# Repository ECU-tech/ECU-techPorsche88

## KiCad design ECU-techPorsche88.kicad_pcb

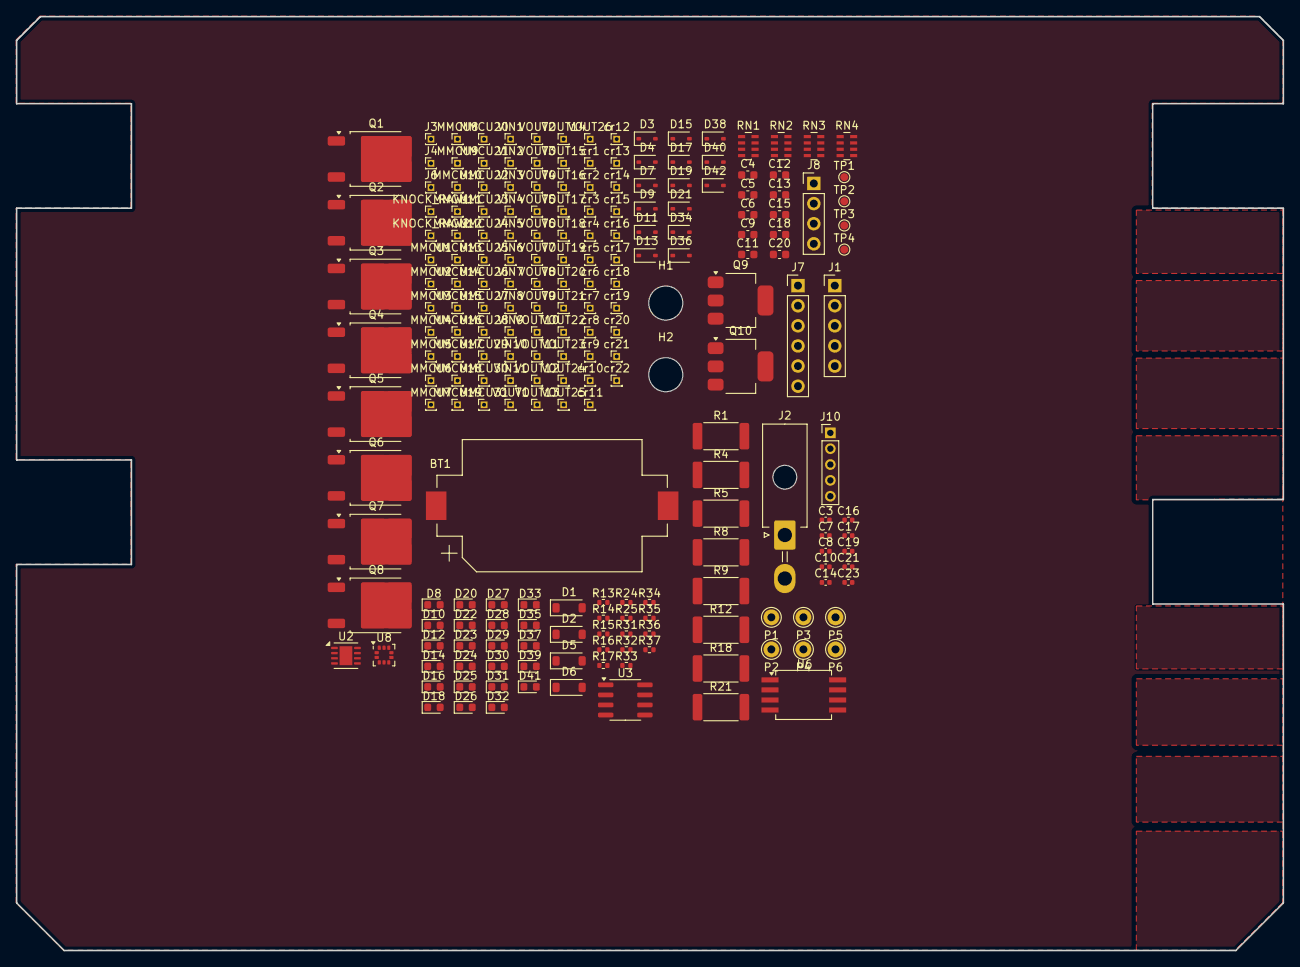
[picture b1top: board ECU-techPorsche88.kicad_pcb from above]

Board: 4 copper layers, 160.0 x 118.0 mm, 215 parts (0 on the bottom side), 69 nets, no tracks yet.

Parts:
BT1: BATTERY_CR2032; BatteryHolder_Keystone_1060_1x2032
C3, C7, C16, C17, C19, C21, C23: 100nF; C_0402_1005Metric
C4, C5, C6, C9, C11, C12, C13, C15, C18, C20: 10u; C_0603_1608Metric
C8: 5.6nF; C_0402_1005Metric
C10: 10nF; C_0402_1005Metric
C14: 220nF; C_0402_1005Metric
D1, D2, D5, D6: B5819W; D_SOD-123
D3, D4, D7, D9, D11, D13, D15, D17, D19, D21, D34, D36, D38, D40, D42: 1N4148WS; D_SOD-323
D8, D10, D12, D14, D16, D18, D20, D22, D37, D39: LED-RED-0603; LED_0603_1608Metric
D23, D24, D25, D26, D27, D28, D29, D30: LED-BLUE-0603; LED_0603_1608Metric
D31, D32, D33, D35: LED-GREEN-0603; LED_0603_1608Metric
D41: LED-WHITE-0603; LED_0603_1608Metric
H1, H2: MountingHole; MountingHole_4.3mm_M4_DIN965
J1: Conn_01x05; PinHeader_1x05_P2.54mm_Vertical
J2: MiniFit; Molex_Mini-Fit_Jr_5569-02A2_2x01_P4.20mm_Horizontal
J3: VRIN1; PinHeader_1x01_P1.00mm_Vertical
J4: VRIN2; PinHeader_1x01_P1.00mm_Vertical
J6: VROUT1; PinHeader_1x01_P1.00mm_Vertical
J7: ETB; PinHeader_1x06_P2.54mm_Vertical
J8: PPS; PinHeader_1x04_P2.54mm_Vertical
J10: Conn_01x05; PinHeader_1x05_P2.00mm_Vertical
KNOCK_RAW1: IN_KNOCK1_RAW; PinHeader_1x01_P1.00mm_Vertical
KNOCK_RAW2: IN_KNOCK2_RAW; PinHeader_1x01_P1.00mm_Vertical
MMCU1, MMCU2, MMCU3, MMCU4, MMCU5, MMCU6, MMCU7, MMCU8, MMCU9, MMCU10, MMCU11, MMCU12, MMCU13, MMCU14, MMCU15, MMCU16, MMCU17, MMCU18, MMCU19, MMCU20, MMCU21, MMCU22, MMCU23, MMCU24, MMCU25, MMCU26, MMCU27, MMCU28, MMCU29, MMCU30, MMCU31: MMCU; PinHeader_1x01_P1.00mm_Vertical
P1, P2, P3, P4, P5, P6: P; Pin_D1.0mm_L10.0mm
Q1, Q2, Q3, Q4, Q5, Q6, Q7, Q8: NGD8201AN; TO-252-2
Q9, Q10: AUIPS2041LTR; SOT-223
R1, R4, R5, R8, R9, R12, R18, R21: DNP; R_2512_6332Metric
R13, R14: DNP; R_0402_1005Metric
R15: 100k; R_0402_1005Metric
R16: 100; R_0402_1005Metric
R17, R24, R25: 10k; R_0402_1005Metric
R31: 1k6; R_0402_1005Metric
R32: 750R; R_0402_1005Metric
R33, R34, R35: 5k1; R_0402_1005Metric
R36: 20k; R_0402_1005Metric
R37: 4.7k; R_0402_1005Metric
RN1, RN2: 4.7k; R_Array_Concave_4x0603
RN3, RN4: 1k; R_Array_Concave_4x0603
TP1, TP2, TP3, TP4: TestPoint; TestPoint_Pad_D1.0mm
U2: TLS115_SON; HVSON-8-1EP_3x3mm_P0.65mm_EP1.6x2.4mm
U3: MCP6002-xSN; SOIC-8_3.9x4.9mm_P1.27mm
U6: MPXA6115A; SSO-8_6.8x5.9mm_P1.27mm_Clearance7mm
U8: LPS25HB; ST_HLGA-10_2.5x2.5mm_P0.6mm_LayoutBorder3x2y
VIN1: VIN9; PinHeader_1x01_P1.00mm_Vertical
VIN2, VIN3, VIN4, VIN5, VIN6, VIN7, VIN8: VIN8; PinHeader_1x01_P1.00mm_Vertical
VIN9: VIN10; PinHeader_1x01_P1.00mm_Vertical
VIN10: VIN16; PinHeader_1x01_P1.00mm_Vertical
VIN11: VIN17; PinHeader_1x01_P1.00mm_Vertical
VOUT1, VOUT2, VOUT3, VOUT4, VOUT5, VOUT6, VOUT7, VOUT8, VOUT9, VOUT10, VOUT11, VOUT12, VOUT14, VOUT15, VOUT16, VOUT17, VOUT19, VOUT20, VOUT21, VOUT22, VOUT23, VOUT24, VOUT25, VOUT26: VOUT4; PinHeader_1x01_P1.00mm_Vertical
VOUT13: VOUT5; PinHeader_1x01_P1.00mm_Vertical
VOUT18: VOUT6; PinHeader_1x01_P1.00mm_Vertical
cr1, cr2, cr3, cr4, cr5, cr6, cr7, cr8, cr9, cr10, cr11, cr12, cr13, cr14, cr15, cr16, cr17, cr18, cr19, cr20, cr21, cr22: cr; PinHeader_1x01_P1.00mm_Vertical

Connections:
+3V3: C23.1, D32.2 (A), J1.3, TP3.1, U8.1 (VDDio), U8.6 (~CS), U8.10 (VDD)
+5V: C3.1, D31.2 (A), J1.4, R37.1, TP2.1, U2.5 (ADJ), U3.8 (V+)
+5VA: C7.1, C17.1, U6.2 (Vcc)
+5VP: J7.1, J7.2, J8.1, U2.1 (OUT)
+12V: D33.2 (A), D34.1 (K), TP4.1
+12V_RAW: C6.1, C9.1, C11.1, C12.1, C13.1, C14.1, C15.1, C16.1, C18.1, C19.1, C20.1, D1.1 (K), D2.1 (K), D3.2 (A), D5.1 (K), D6.1 (K), D35.2 (A), D36.1 (K), J1.5, R36.1
/12V_prot: RN1.1 (R1.1), RN1.2 (R2.1), RN1.3 (R3.1), RN1.4 (R4.1), RN2.1 (R1.1), RN2.2 (R2.1), RN2.3 (R3.1), RN2.4 (R4.1), U2.7 (EN), U2.8 (IN), VOUT18.1
/COIL_1: Q1.2 (C), R1.1
/COIL_2: Q5.2 (C), R9.1
/COIL_3: Q4.2 (C), R8.2
/COIL_4: Q3.2 (C), R5.1
/COIL_5: Q2.2 (C), R4.2
/COIL_6: Q6.2 (C), R12.2
/COIL_7: Q7.2 (C), R18.1
/COIL_8: Q8.2 (C), R21.2
/ETB_EN: R15.2, R17.2
/ICV: Q9.1 (IN), R24.2
/IDLE: Q10.1 (IN), R25.2
/IN_CRANK: D41.1 (K), D42.2 (A), R13.2
/OUT_FUEL_PUMP_RELAY: D39.1 (K), D40.2 (A)
/OUT_ICV: D5.2 (A), Q9.2 (D), cr22.1
/OUT_IDLE: D6.2 (A), Q10.2 (D)
/OUT_IGN1: D30.2 (A), R1.2
/OUT_IGN2: D26.2 (A), R9.2
/OUT_IGN3: D29.2 (A), R8.1
/OUT_IGN4: D25.2 (A), R5.2
/OUT_IGN5: D28.2 (A), R4.1
/OUT_IGN6: D24.2 (A), R12.1
/OUT_IGN7: D27.2 (A), R18.2
/OUT_IGN8: D23.2 (A), R21.1
/OUT_INJ1: D7.2 (A), D8.1 (K)
/OUT_INJ2: D9.2 (A), D10.1 (K)
/OUT_INJ3: D11.2 (A), D12.1 (K)
/OUT_INJ4: D13.2 (A), D14.1 (K)
/OUT_INJ5: D15.2 (A), D16.1 (K)
/OUT_INJ6: D17.2 (A), D18.1 (K)
/OUT_INJ7: D19.2 (A), D20.1 (K)
/OUT_INJ8: D21.2 (A), D22.1 (K)
/OUT_MAIN_RELAY: D37.2 (A), D38.1 (K)
GND: BT1.2 (-), C3.2, C6.2, C7.2, C8.2, C9.2, C11.2, C12.2, C13.2, C15.2, C16.2, C17.2, C18.2, C19.2, C20.2, C21.2, C23.2, J1.1, J1.2, J7.5, J7.6, J8.4, J10.5, P1.1, Q1.3 (E), Q2.3 (E), Q3.3 (E), Q4.3 (E), Q5.3 (E), Q6.3 (E), Q7.3 (E), Q8.3 (E), Q9.3 (S), Q10.3 (S), R17.1, R24.1, R25.1, R31.2, R32.2, R33.2, R34.2, R35.2, RN3.1 (R1.1), RN3.2 (R2.1), RN3.3 (R3.1), RN3.4 (R4.1), RN4.1 (R1.1), RN4.2 (R2.1), RN4.3 (R3.1), RN4.4 (R4.1), TP1.1, U2.3 (GND), U2.9 (GND), U3.4 (V-), U6.3 (GND), U8.3 (GND), U8.5 (SA0/MISO), U8.8 (GND), U8.9 (GND)
unnamed: C10.1, R16.1
unnamed: D3.1 (K), D4.2 (A), R16.2
unnamed: C14.2, D4.1 (K)
unnamed: D7.1 (K), D8.2 (A), RN1.5 (R4.2)
unnamed: D9.1 (K), D10.2 (A), RN1.6 (R3.2)
unnamed: D11.1 (K), D12.2 (A), RN1.7 (R2.2)
unnamed: D13.1 (K), D14.2 (A), RN1.8 (R1.2)
unnamed: D15.1 (K), D16.2 (A), RN2.5 (R4.2)
unnamed: D17.1 (K), D18.2 (A), RN2.6 (R3.2)
unnamed: D19.1 (K), D20.2 (A), RN2.7 (R2.2)
unnamed: D21.1 (K), D22.2 (A), RN2.8 (R1.2)
unnamed: D23.1 (K), RN3.5 (R4.2)
unnamed: D24.1 (K), RN3.7 (R2.2)
unnamed: D25.1 (K), RN4.5 (R4.2)
unnamed: D26.1 (K), RN4.7 (R2.2)
unnamed: D27.1 (K), RN3.6 (R3.2)
unnamed: D28.1 (K), RN3.8 (R1.2)
unnamed: D29.1 (K), RN4.6 (R3.2)
unnamed: D30.1 (K), RN4.8 (R1.2)
unnamed: D31.1 (K), R31.1
unnamed: D32.1 (K), R32.1
unnamed: D33.1 (K), D34.2 (A), R33.1
unnamed: D35.1 (K), D36.2 (A), R34.1
unnamed: D37.1 (K), D38.2 (A), R35.1
unnamed: D39.2 (A), D40.1 (K), R36.2
unnamed: D41.2 (A), D42.1 (K), R37.2
unnamed: C4.1, U3.1, U3.2 (-)
unnamed: C5.1, U3.6 (-), U3.7
unnamed: C8.1, R15.1

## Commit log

2024-07-24 test
2024-07-24 [skip actions] Auto-generated board v2.1
2024-07-24 Rename bom_replace_xxxyyy-a.csv to bom_replace_ECU-techPorsche88-a.csv
